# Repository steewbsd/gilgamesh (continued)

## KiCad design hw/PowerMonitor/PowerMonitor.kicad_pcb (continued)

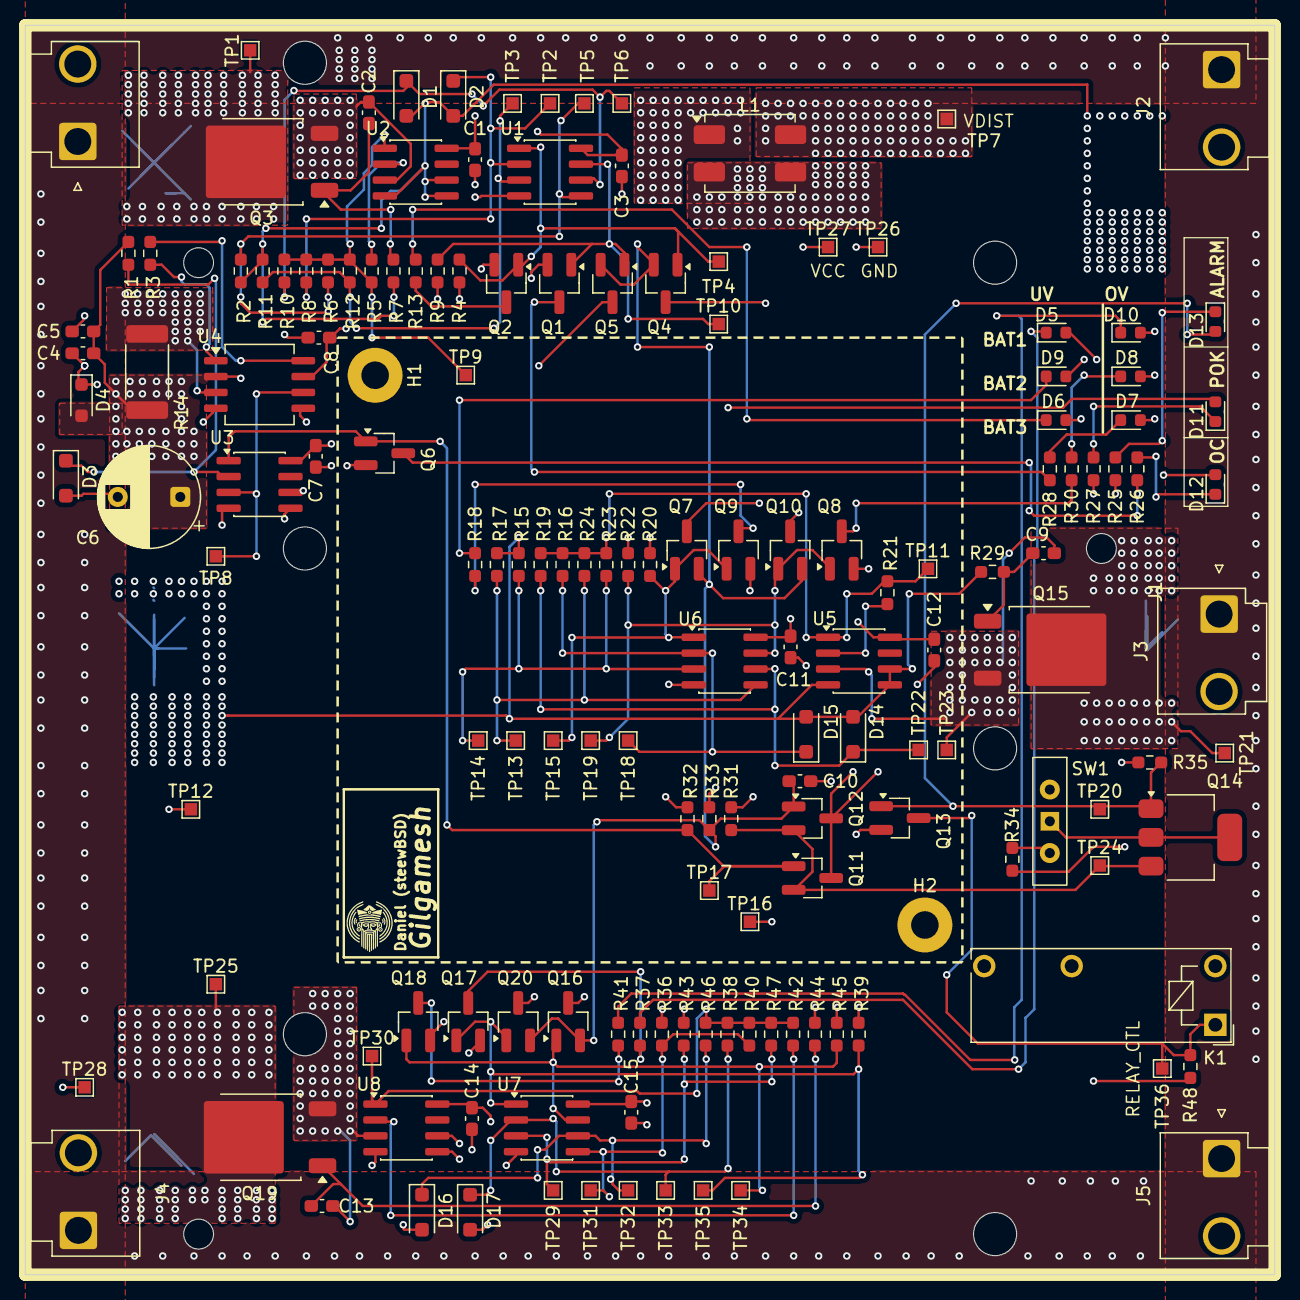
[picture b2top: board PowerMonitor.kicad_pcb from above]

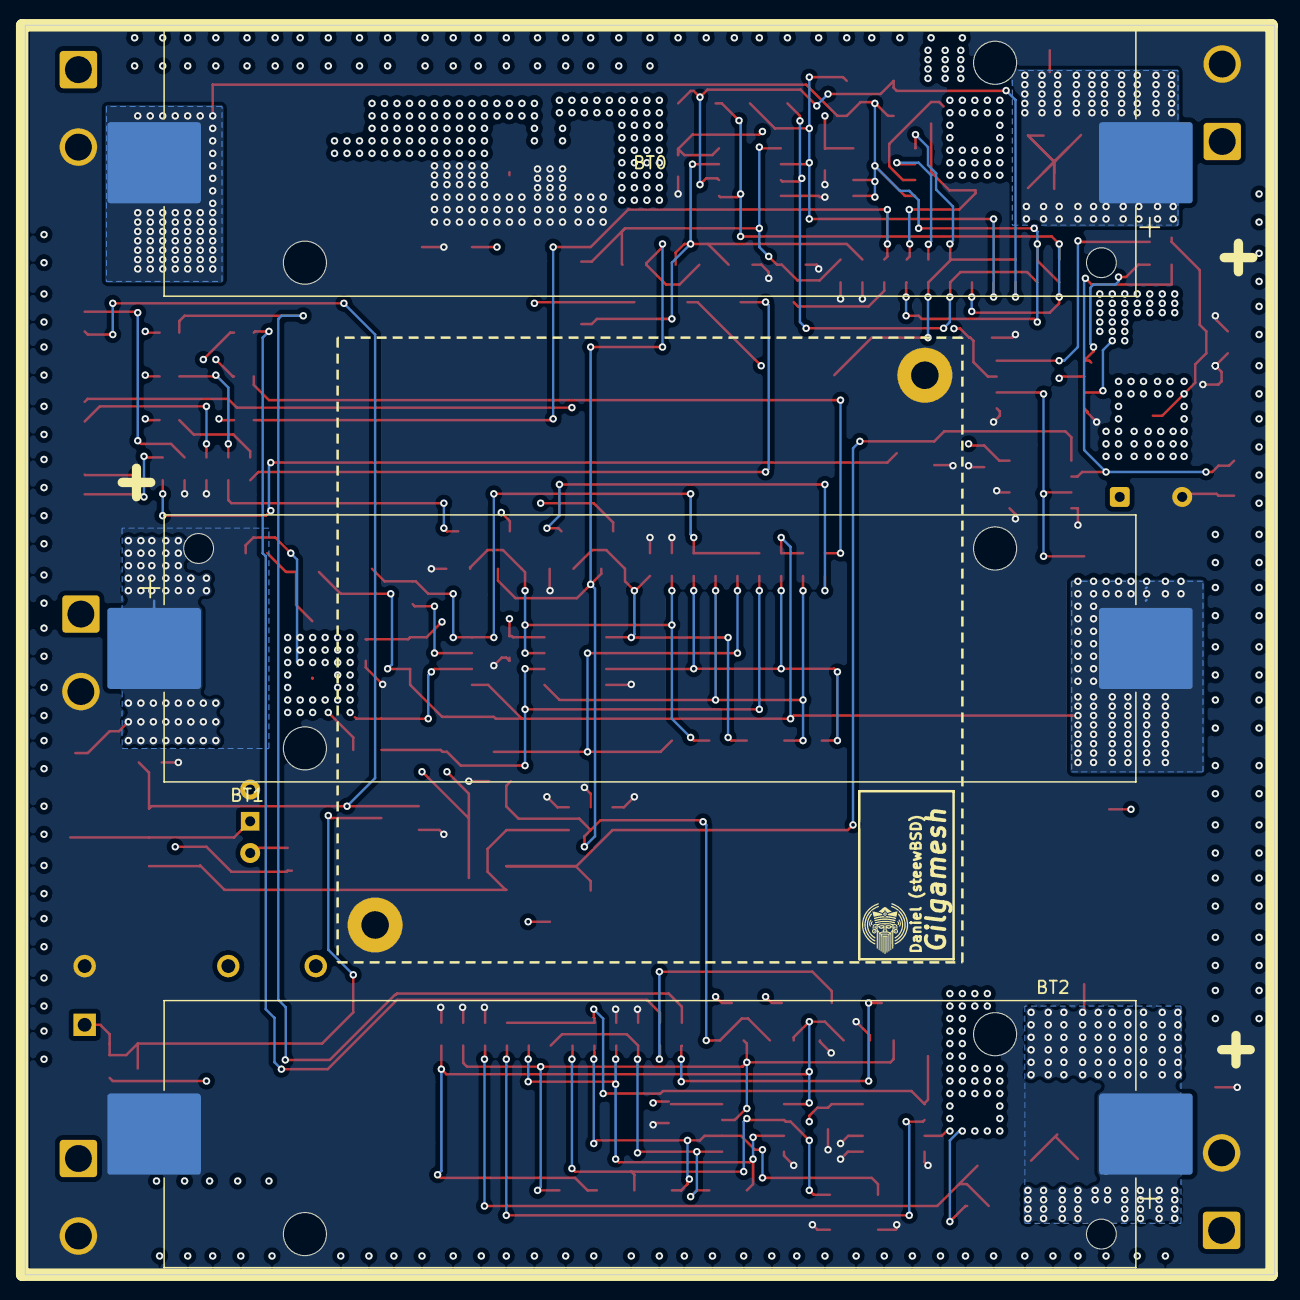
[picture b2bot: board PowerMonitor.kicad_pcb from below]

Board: 4 copper layers, 100.0 x 100.0 mm, 157 parts (3 on the bottom side), 64 nets.

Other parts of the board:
R2: 2k; R_0603_1608Metric_Pad0.98x0.95mm_HandSolder

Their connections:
/CellMonitor2/Vprot: R2.1; also elsewhere on the board
unnamed 54: R2.2; also elsewhere on the board

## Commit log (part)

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2026-01-11 Split the MPU data UART tx into another thread
2026-01-11 Perform cargo fmt
2026-01-13 Replace octave with matplotlib
2026-01-17 Add plotting ypr
2026-01-17 Send quaternions instead of ypr
2026-02-01 fctrl: implement CAN baseline communication, control loop start
2026-02-02 Implement Frame type
2026-02-07 Rework powermon
2026-03-04 ad uvov in powermon, overcurrent and prepare for latch alarm
2026-03-08 * hw/PowerMonitor/CellMonitor.kicad_sch: start PCB layout
2026-03-08 finish PowerMonitor placement
2026-04-02 powmon: advance routing
2026-04-02 powmon: finish routing
2026-04-02 powmon: pre-fab board finishes
2026-04-03 powmon: add more vias for power signals
2026-04-04 powmon: change plane connections to solid and add vias
2026-04-04 powmon: more thermal considerations
2026-04-04 powmon: update to kicad 10
2026-04-05 remote_ctrl: start working on it
2026-04-12 remote_ctrl: add radio and change mcu
2026-04-19 remote_ctrl: finish schematic
2026-04-19 remote_ctrl: re-start PCB
2026-04-19 remote_ctrl: basic PCB shape
2026-04-20 remote_ctrl: start laying out RF components
2026-04-20 remote_ctrl: add RF net class
2026-05-24 remote_ctrl: half way to placement, replace max1473 wit, micrf220
2026-05-31 remote_ctrl: continue placemen
2026-05-31 remote_ctrl: pre-outline modifications
2026-06-01 remote_ctrl: finish placement
2026-06-01 remote_ctrl: align everything pre-route
2026-06-02 remote_ctrl: fix some schematic issues, add battery PTC
2026-06-07 remote_ctrl: advance routing
2026-06-07 remote_ctrl: finish preliminary routing
2026-06-08 remote_ctrl: final touches
2026-06-27 remote_ctrl: change logdet to AD8314 and battery holder to SMD
2026-06-27 remote_ctrl: finish new layout with components changed
2026-06-27 remote_ctrl: finish teardrops and DRC
